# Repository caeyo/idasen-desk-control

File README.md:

# idasen-desk-control
Firmware/PCB files for a physical device to control a Idasen desk's height via saving/applying presets. 

Created as my first foray into electronics hardware (and out of spite for the manufacturer's mobile app).

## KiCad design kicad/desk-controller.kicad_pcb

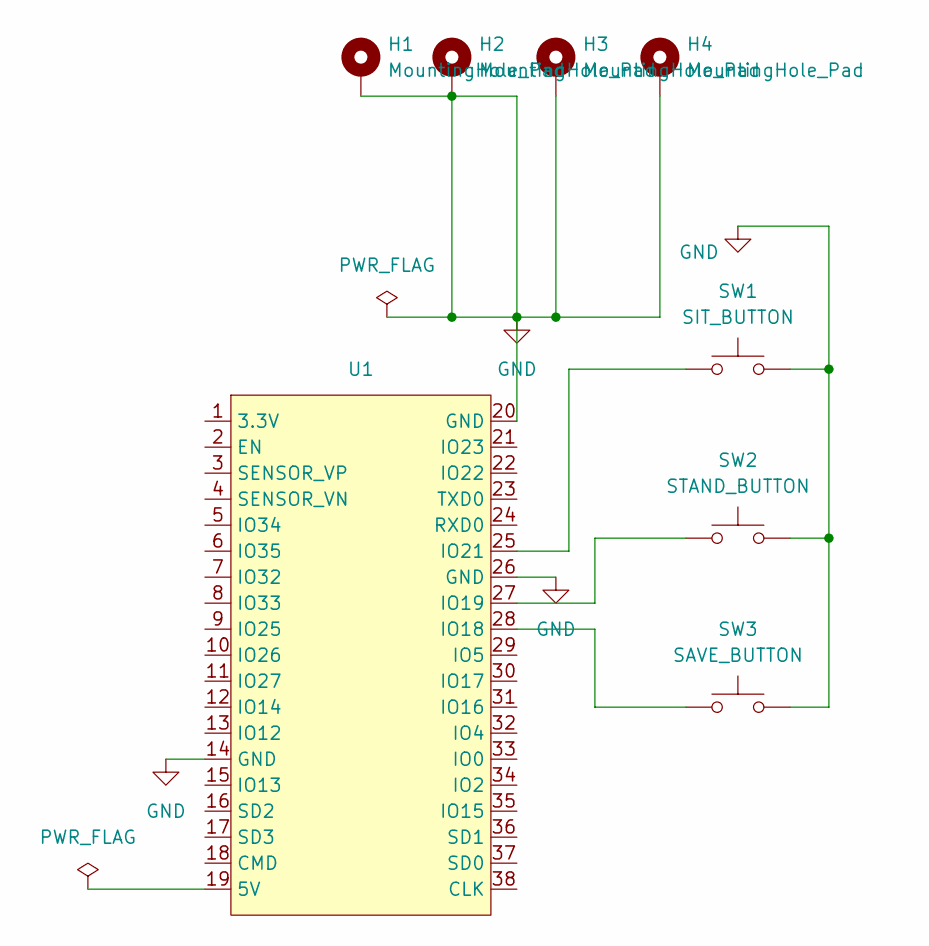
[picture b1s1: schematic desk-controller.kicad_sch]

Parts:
H1, H2, H3, H4: MountingHole_Pad; MountingHole_3.2mm_M3_Pad_Via
SW1: SIT_BUTTON; SW_PUSH_6mm_H5mm
SW2: STAND_BUTTON; SW_PUSH_6mm_H5mm
SW3: SAVE_BUTTON; SW_PUSH_6mm_H5mm
U1: esp32-keyestudio-devboard

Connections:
GND: H1.1, H2.1, H3.1, H4.1, SW1.2, SW2.2, SW3.2, U1.14 (GND), U1.20 (GND), U1.26 (GND)
unnamed: SW3.1, U1.28 (IO18)
unnamed: SW2.1, U1.27 (IO19)
unnamed: SW1.1, U1.25 (IO21)

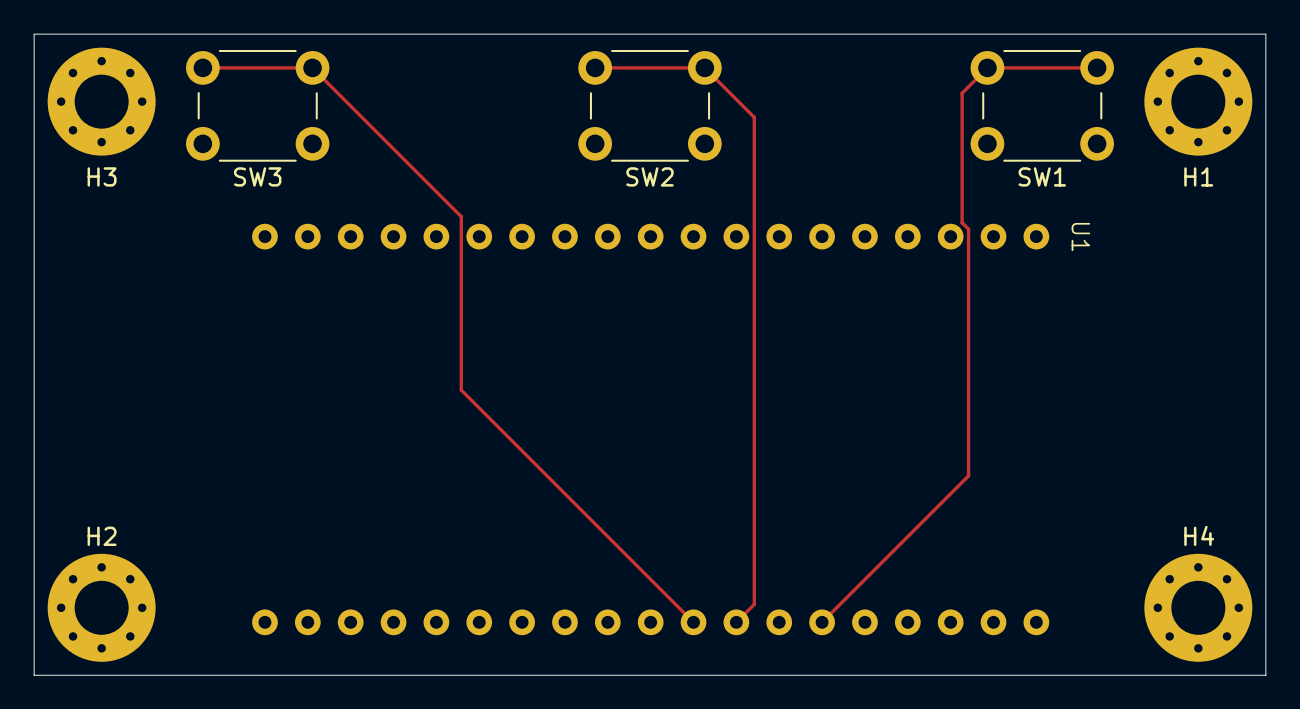
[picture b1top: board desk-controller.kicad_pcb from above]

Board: 2 copper layers, 73.0 x 38.0 mm, 8 parts (0 on the bottom side), 4 nets.

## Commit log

2026-02-10 Project files
2026-02-10 Add gitignore for kicad files
2026-02-10 Sync with gitignore
